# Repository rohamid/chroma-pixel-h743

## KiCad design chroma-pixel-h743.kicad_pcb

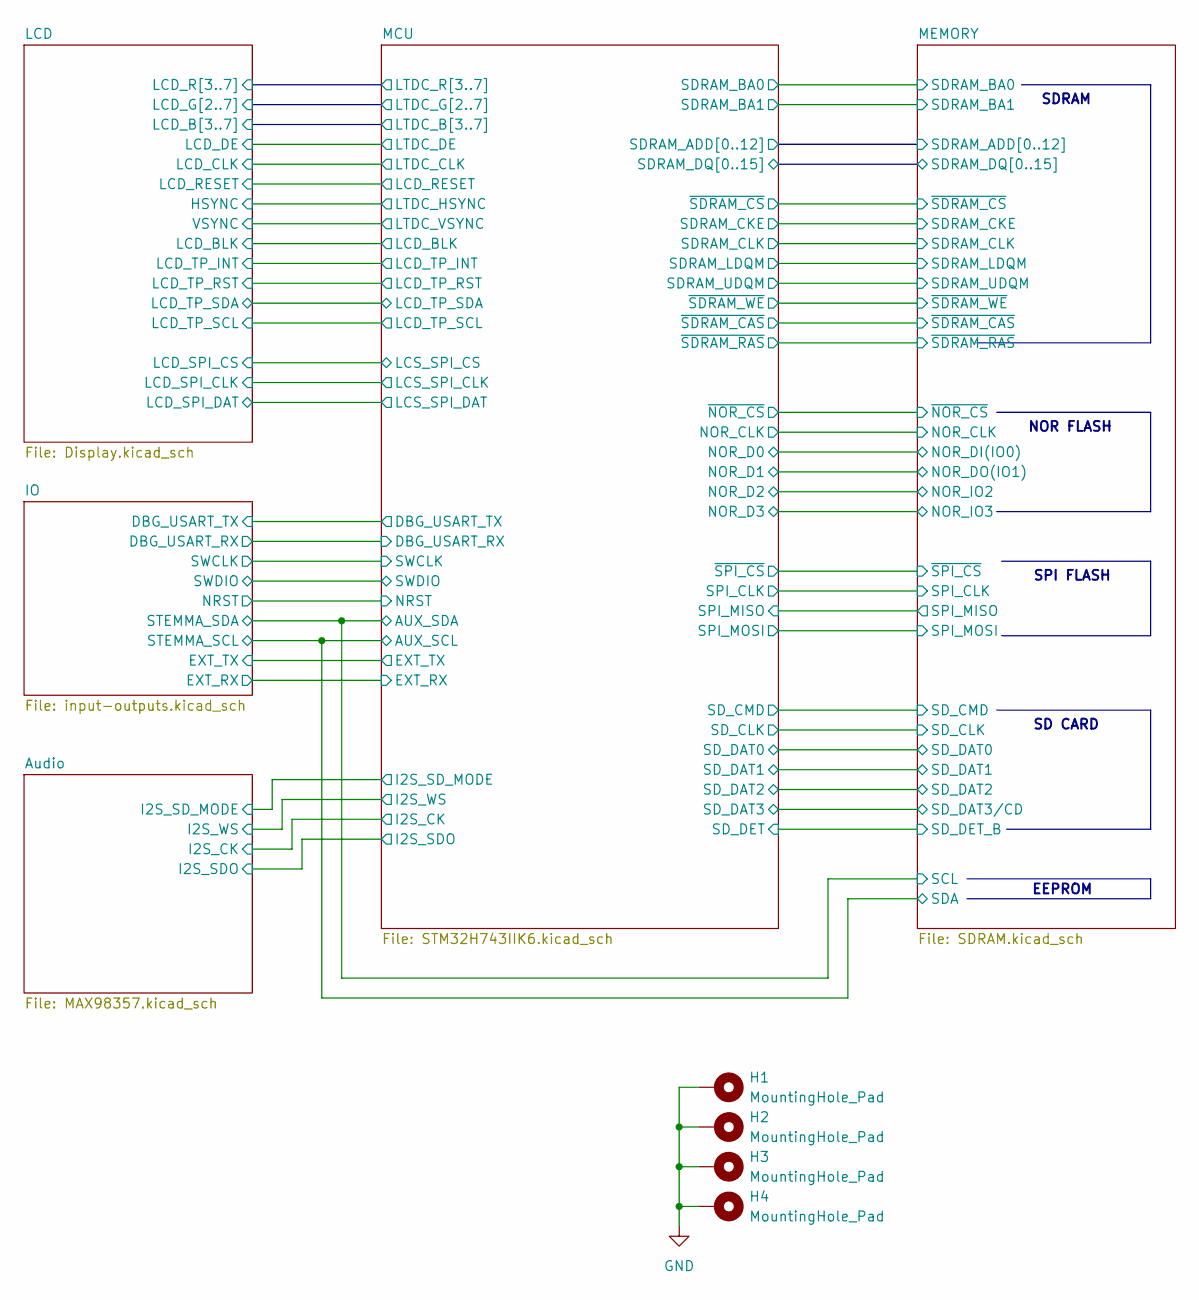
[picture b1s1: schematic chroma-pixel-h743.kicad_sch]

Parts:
H1, H2, H3, H4: MountingHole_Pad; MountingHole_3.2mm_M3_Pad_Via

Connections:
GND: H1.1, H2.1, H3.1, H4.1; also elsewhere on the board

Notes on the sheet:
SD CARD
NOR FLASH
SPI FLASH
SDRAM
EEPROM

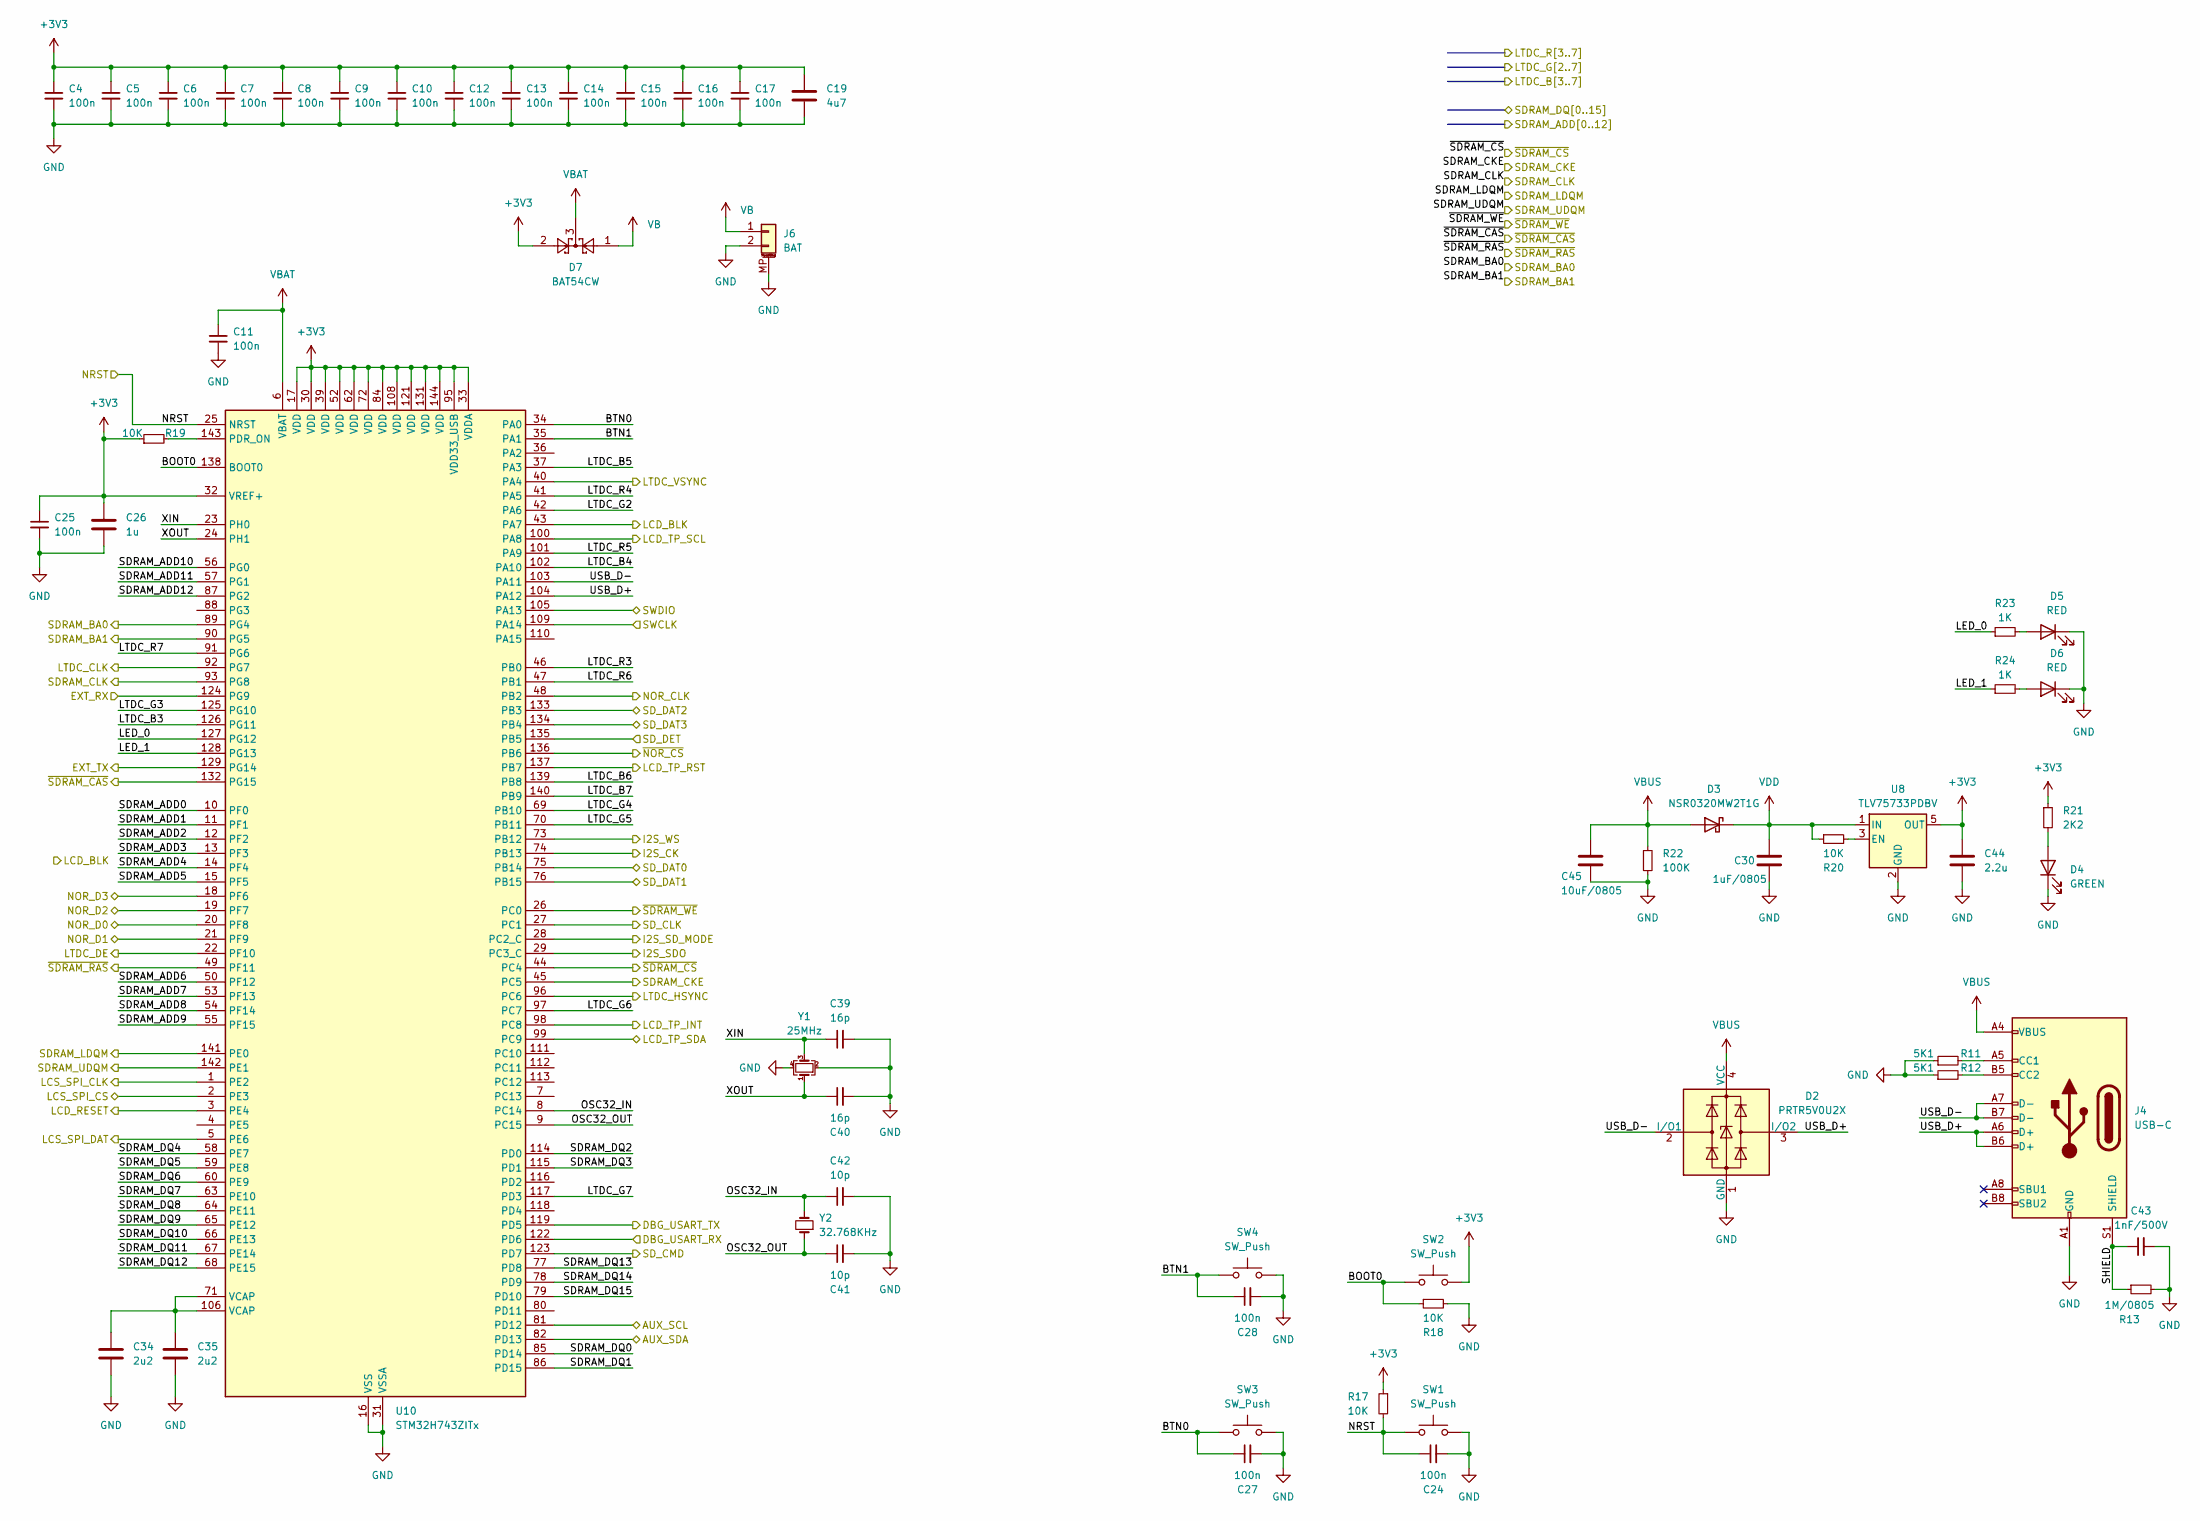
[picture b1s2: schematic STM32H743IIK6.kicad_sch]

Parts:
C4, C5, C6, C7, C8, C9, C10, C11, C12, C13, C14, C15, C16, C17, C24, C25, C27, C28: 100n; C_0402_1005Metric; JLCPCB Part # C307331
C19: 4u7; C_0603_1608Metric; JLCPCB Part # C19666
C26: 1u; C_0603_1608Metric; JLCPCB Part # C15849
C30: 1uF/0805; C_0805_2012Metric; JLCPCB Part # C28323
C34, C35: 2u2; C_0603_1608Metric; JLCPCB Part # C23630
C39, C40: 16p; C_0402_1005Metric; JLCPCB Part # C77590
C41, C42: 10p; C_0402_1005Metric; JLCPCB Part # C32949
C43: 1nF/500V; C_1206_3216Metric; JLCPCB Part # C35216
C44: 2.2u; C_0805_2012Metric; JLCPCB Part # C377773
C45: 10uF/0805; C_0805_2012Metric; JLCPCB Part # C440198
D2: PRTR5V0U2X; SOT-143; JLCPCB Part # C12333
D3: NSR0320MW2T1G; D_SOD-323; JLCPCB Part # C48192
D4: GREEN; LED_0805_2012Metric; JLCPCB Part # C2297
D5, D6: RED; LED_0805_2012Metric; JLCPCB Part # C84256
D7: BAT54CW; SOT-23; JLCPCB Part # C37704
J4: USB-C; USB_C_Receptacle_G-Switch_GT-USB-7010ASV; JLCPCB Part # C963412
J6: BAT; Hirose_DF13C_CL535-0402-2-51_1x02-1MP_P1.25mm_Vertical; JLCPCB Part # C7419891
R11, R12: 5K1; R_0402_1005Metric; JLCPCB Part # C25905
R13: 1M/0805; R_0805_2012Metric; JLCPCB Part # C17514
R17, R18, R19, R20: 10K; R_0402_1005Metric; JLCPCB Part # C25744
R21: 2K2; R_0402_1005Metric; JLCPCB Part # C25879
R22: 100K; R_0402_1005Metric; JLCPCB Part # C60491
R23, R24: 1K; R_0402_1005Metric; JLCPCB Part # C11702
SW1, SW2, SW3, SW4: SW_Push; SW_SPST_PTS810; JLCPCB Part # C127488
U8: TLV75733PDBV; SOT-23-5; JLCPCB Part # C485517
U10: STM32H743ZITx; LQFP-144_20x20mm_P0.5mm; JLCPCB Part # C114408
Y1: 25MHz; Crystal_SMD_2520-4Pin_2.5x2.0mm; JLCPCB Part # C255954
Y2: 32.768KHz; Crystal_SMD_2012-2Pin_2.0x1.2mm; JLCPCB Part # C99009

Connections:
+3V3: C4.1, C5.1, C6.1, C7.1, C8.1, C9.1, C10.1, C12.1, C13.1, C14.1, C15.1, C16.1, C17.1, C19.1, C25.1, C26.1, C44.1, D7.2, R17.1, R19.1, R21.1, SW2.2, U8.5 (OUT), U10.17 (VDD), U10.30 (VDD), U10.32 (VREF+), U10.33 (VDDA), U10.39 (VDD), U10.52 (VDD), U10.62 (VDD), U10.72 (VDD), U10.84 (VDD), U10.95 (VDD33_USB), U10.108 (VDD), U10.121 (VDD), U10.131 (VDD), U10.144 (VDD); also elsewhere on the board
/Audio/I2S_CK: U10.74 (PB13); also elsewhere on the board
/Audio/I2S_SDO: U10.29 (PC3_C); also elsewhere on the board
/Audio/I2S_SD_MODE: U10.28 (PC2_C); also elsewhere on the board
/Audio/I2S_WS: U10.73 (PB12); also elsewhere on the board
/IO/DBG_USART_RX: U10.122 (PD6); also elsewhere on the board
/IO/DBG_USART_TX: U10.119 (PD5); also elsewhere on the board
/IO/EXT_RX: U10.124 (PG9); also elsewhere on the board
/IO/EXT_TX: U10.129 (PG14); also elsewhere on the board
/IO/NRST: C24.1, R17.2, SW1.1, U10.25 (NRST); also elsewhere on the board
/IO/STEMMA_SCL: U10.81 (PD12); also elsewhere on the board
/IO/STEMMA_SDA: U10.82 (PD13); also elsewhere on the board
/IO/SWCLK: U10.109 (PA14); also elsewhere on the board
/IO/SWDIO: U10.105 (PA13); also elsewhere on the board
/LCD/HSYNC: U10.96 (PC6); also elsewhere on the board
/LCD/LCD_B3: U10.126 (PG11); also elsewhere on the board
/LCD/LCD_B4: U10.102 (PA10); also elsewhere on the board
/LCD/LCD_B5: U10.37 (PA3); also elsewhere on the board
/LCD/LCD_B6: U10.139 (PB8); also elsewhere on the board
/LCD/LCD_B7: U10.140 (PB9); also elsewhere on the board
/LCD/LCD_BLK: U10.43 (PA7); also elsewhere on the board
/LCD/LCD_CLK: U10.92 (PG7); also elsewhere on the board
/LCD/LCD_DE: U10.22 (PF10); also elsewhere on the board
/LCD/LCD_G2: U10.42 (PA6); also elsewhere on the board
/LCD/LCD_G3: U10.125 (PG10); also elsewhere on the board
/LCD/LCD_G4: U10.69 (PB10); also elsewhere on the board
/LCD/LCD_G5: U10.70 (PB11); also elsewhere on the board
/LCD/LCD_G6: U10.97 (PC7); also elsewhere on the board
/LCD/LCD_G7: U10.117 (PD3); also elsewhere on the board
/LCD/LCD_R3: U10.46 (PB0); also elsewhere on the board
/LCD/LCD_R4: U10.41 (PA5); also elsewhere on the board
/LCD/LCD_R5: U10.101 (PA9); also elsewhere on the board
/LCD/LCD_R6: U10.47 (PB1); also elsewhere on the board
/LCD/LCD_R7: U10.91 (PG6); also elsewhere on the board
/LCD/LCD_RESET: U10.3 (PE4); also elsewhere on the board
/LCD/LCD_SPI_CLK: U10.1 (PE2); also elsewhere on the board
/LCD/LCD_SPI_CS: U10.2 (PE3); also elsewhere on the board
/LCD/LCD_SPI_DAT: U10.5 (PE6); also elsewhere on the board
/LCD/LCD_TP_INT: U10.98 (PC8); also elsewhere on the board
/LCD/LCD_TP_RST: U10.137 (PB7); also elsewhere on the board
/LCD/LCD_TP_SCL: U10.100 (PA8); also elsewhere on the board
/LCD/LCD_TP_SDA: U10.99 (PC9); also elsewhere on the board
/LCD/VSYNC: U10.40 (PA4); also elsewhere on the board
/MCU/BOOT0: R18.1, SW2.1, U10.138 (BOOT0)
/MCU/BTN0: C27.1, SW3.1, U10.34 (PA0)
/MCU/BTN1: C28.1, SW4.1, U10.35 (PA1)
/MCU/LED_0: R23.1, U10.127 (PG12)
/MCU/LED_1: R24.1, U10.128 (PG13)
/MCU/OSC32_IN: C42.1, U10.8 (PC14), Y2.2
/MCU/OSC32_OUT: C41.1, U10.9 (PC15), Y2.1
/MCU/SDRAM_ADD0: U10.10 (PF0); also elsewhere on the board
/MCU/SDRAM_ADD1: U10.11 (PF1); also elsewhere on the board
/MCU/SDRAM_ADD2: U10.12 (PF2); also elsewhere on the board
/MCU/SDRAM_ADD3: U10.13 (PF3); also elsewhere on the board
/MCU/SDRAM_ADD4: U10.14 (PF4); also elsewhere on the board
/MCU/SDRAM_ADD5: U10.15 (PF5); also elsewhere on the board
/MCU/SDRAM_ADD6: U10.50 (PF12); also elsewhere on the board
/MCU/SDRAM_ADD7: U10.53 (PF13); also elsewhere on the board
/MCU/SDRAM_ADD8: U10.54 (PF14); also elsewhere on the board
/MCU/SDRAM_ADD9: U10.55 (PF15); also elsewhere on the board
/MCU/SDRAM_ADD10: U10.56 (PG0); also elsewhere on the board
/MCU/SDRAM_ADD11: U10.57 (PG1); also elsewhere on the board
/MCU/SDRAM_ADD12: U10.87 (PG2); also elsewhere on the board
/MCU/SDRAM_BA0: U10.89 (PG4); also elsewhere on the board
/MCU/SDRAM_BA1: U10.90 (PG5); also elsewhere on the board
/MCU/SDRAM_CKE: U10.45 (PC5); also elsewhere on the board
/MCU/SDRAM_CLK: U10.93 (PG8); also elsewhere on the board
/MCU/SDRAM_DQ0: U10.85 (PD14); also elsewhere on the board
/MCU/SDRAM_DQ1: U10.86 (PD15); also elsewhere on the board
/MCU/SDRAM_DQ2: U10.114 (PD0); also elsewhere on the board
/MCU/SDRAM_DQ3: U10.115 (PD1); also elsewhere on the board
/MCU/SDRAM_DQ4: U10.58 (PE7); also elsewhere on the board
/MCU/SDRAM_DQ5: U10.59 (PE8); also elsewhere on the board
/MCU/SDRAM_DQ6: U10.60 (PE9); also elsewhere on the board
/MCU/SDRAM_DQ7: U10.63 (PE10); also elsewhere on the board
/MCU/SDRAM_DQ8: U10.64 (PE11); also elsewhere on the board
/MCU/SDRAM_DQ9: U10.65 (PE12); also elsewhere on the board
/MCU/SDRAM_DQ10: U10.66 (PE13); also elsewhere on the board
/MCU/SDRAM_DQ11: U10.67 (PE14); also elsewhere on the board
/MCU/SDRAM_DQ12: U10.68 (PE15); also elsewhere on the board
/MCU/SDRAM_DQ13: U10.77 (PD8); also elsewhere on the board
/MCU/SDRAM_DQ14: U10.78 (PD9); also elsewhere on the board
/MCU/SDRAM_DQ15: U10.79 (PD10); also elsewhere on the board
/MCU/SDRAM_LDQM: U10.141 (PE0); also elsewhere on the board
/MCU/SDRAM_UDQM: U10.142 (PE1); also elsewhere on the board
/MCU/SHIELD: C43.1, J4.S1 (SHIELD), R13.1
/MCU/USB_D+: D2.3 (I/O2), J4.A6 (D+), J4.B6 (D+), U10.104 (PA12)
/MCU/USB_D-: D2.2 (I/O1), J4.A7 (D-), J4.B7 (D-), U10.103 (PA11)
/MCU/XIN: C39.1, U10.23 (PH0), Y1.3
/MCU/XOUT: C40.1, U10.24 (PH1), Y1.1
/MCU/~SDRAM_CAS: U10.132 (PG15); also elsewhere on the board
/MCU/~SDRAM_CS: U10.44 (PC4); also elsewhere on the board
/MCU/~SDRAM_RAS: U10.49 (PF11); also elsewhere on the board
/MCU/~SDRAM_WE: U10.26 (PC0); also elsewhere on the board
/MEMORY/NOR_CLK: U10.48 (PB2); also elsewhere on the board
/MEMORY/NOR_DI(IO0): U10.20 (PF8); also elsewhere on the board
/MEMORY/NOR_DO(IO1): U10.21 (PF9); also elsewhere on the board
/MEMORY/NOR_IO2: U10.19 (PF7); also elsewhere on the board
/MEMORY/NOR_IO3: U10.18 (PF6); also elsewhere on the board
/MEMORY/SD_CLK: U10.27 (PC1); also elsewhere on the board
/MEMORY/SD_CMD: U10.123 (PD7); also elsewhere on the board
/MEMORY/SD_DAT0: U10.75 (PB14); also elsewhere on the board
/MEMORY/SD_DAT1: U10.76 (PB15); also elsewhere on the board
/MEMORY/SD_DAT2: U10.133 (PB3); also elsewhere on the board
/MEMORY/SD_DAT3/CD: U10.134 (PB4); also elsewhere on the board
/MEMORY/SD_DET: U10.135 (PB5); also elsewhere on the board
/MEMORY/~NOR_CS: U10.136 (PB6); also elsewhere on the board
GND: C4.2, C5.2, C6.2, C7.2, C8.2, C9.2, C10.2, C11.2, C12.2, C13.2, C14.2, C15.2, C16.2, C17.2, C19.2, C24.2, C25.2, C26.2, C27.2, C28.2, C30.2, C34.2, C35.2, C39.2, C40.2, C41.2, C42.2, C43.2, C44.2, C45.2, D2.1 (GND), D4.1 (K), D5.1 (K), D6.1 (K), J4.A1 (GND), J4.A12 (GND), J4.B1 (GND), J4.B12 (GND), J6.2, J6.MP (MountPin), R11.1, R12.1, R13.2, R18.2, R22.2, SW1.2, SW3.2, SW4.2, U8.2 (GND), U10.16 (VSS), U10.31 (VSSA), U10.38 (VSS), U10.51 (VSS), U10.61 (VSS), U10.83 (VSS), U10.94 (VSS), U10.107 (VSS), U10.120 (VSS), U10.130 (VSS), Y1.2, Y1.4; also elsewhere on the board
unnamed: C34.1, C35.1, U10.71 (VCAP), U10.106 (VCAP)
unnamed: D4.2 (A), R21.2
unnamed: D5.2 (A), R23.2
unnamed: D6.2 (A), R24.2
unnamed: J4.A5 (CC1), R11.2
unnamed: J4.B5 (CC2), R12.2
unnamed: R20.2, U8.3 (EN)
unnamed: R19.2, U10.143 (PDR_ON)
VB: D7.1, J6.1
VBAT: C11.1, D7.3, U10.6 (VBAT)
VBUS: C45.1, D2.4 (VCC), D3.2 (A), J4.A4 (VBUS), J4.A9 (VBUS), J4.B4 (VBUS), J4.B9 (VBUS), R22.1; also elsewhere on the board
VDD: C30.1, D3.1 (K), R20.1, U8.1 (IN); also elsewhere on the board

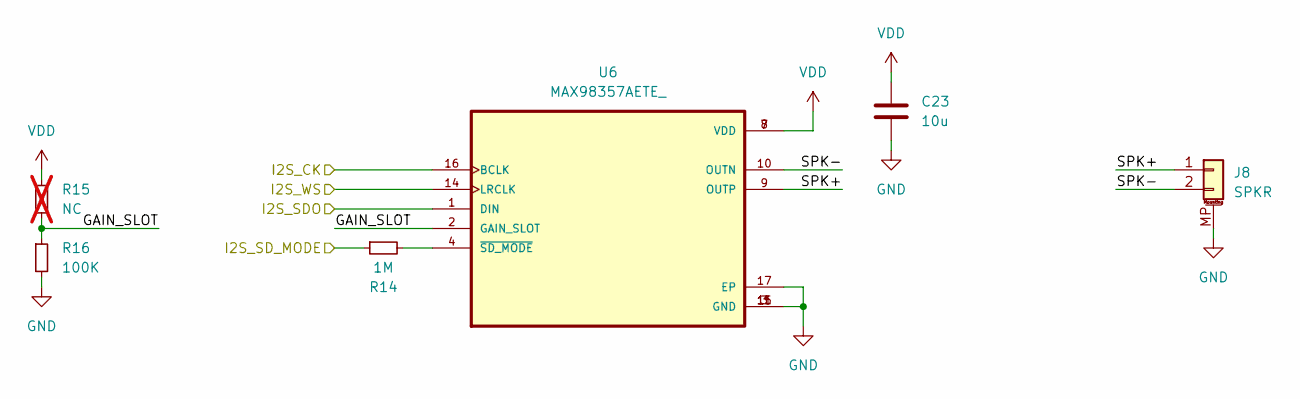
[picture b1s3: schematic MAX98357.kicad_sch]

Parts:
C23: 10u; C_0603_1608Metric; JLCPCB Part # C96446
J8: SPKR; Hirose_DF13C_CL535-0402-2-51_1x02-1MP_P1.25mm_Vertical; JLCPCB Part # C7419891
R14: 1M; R_0402_1005Metric; JLCPCB Part # C26083
R15: NC; R_0402_1005Metric; not fitted
R16: 100K; R_0402_1005Metric; JLCPCB Part # C60491
U6: MAX98357AETE_; QFN50P300X300X80-17N; JLCPCB Part # C910544

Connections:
/Audio/GAIN_SLOT: R15.2, R16.1, U6.2 (GAIN_SLOT)
/Audio/I2S_CK: U6.16 (BCLK); also elsewhere on the board
/Audio/I2S_SDO: U6.1 (DIN); also elsewhere on the board
/Audio/I2S_SD_MODE: R14.1; also elsewhere on the board
/Audio/I2S_WS: U6.14 (LRCLK); also elsewhere on the board
/Audio/SPK+: J8.1, U6.9 (OUTP)
/Audio/SPK-: J8.2, U6.10 (OUTN)
GND: C23.2, J8.MP (MountPin), R16.2, U6.3 (GND), U6.11 (GND), U6.15 (GND), U6.17 (EP); also elsewhere on the board
unnamed: R14.2, U6.4 (~SD_MODE)
VDD: C23.1, R15.1, U6.7 (VDD), U6.8 (VDD); also elsewhere on the board

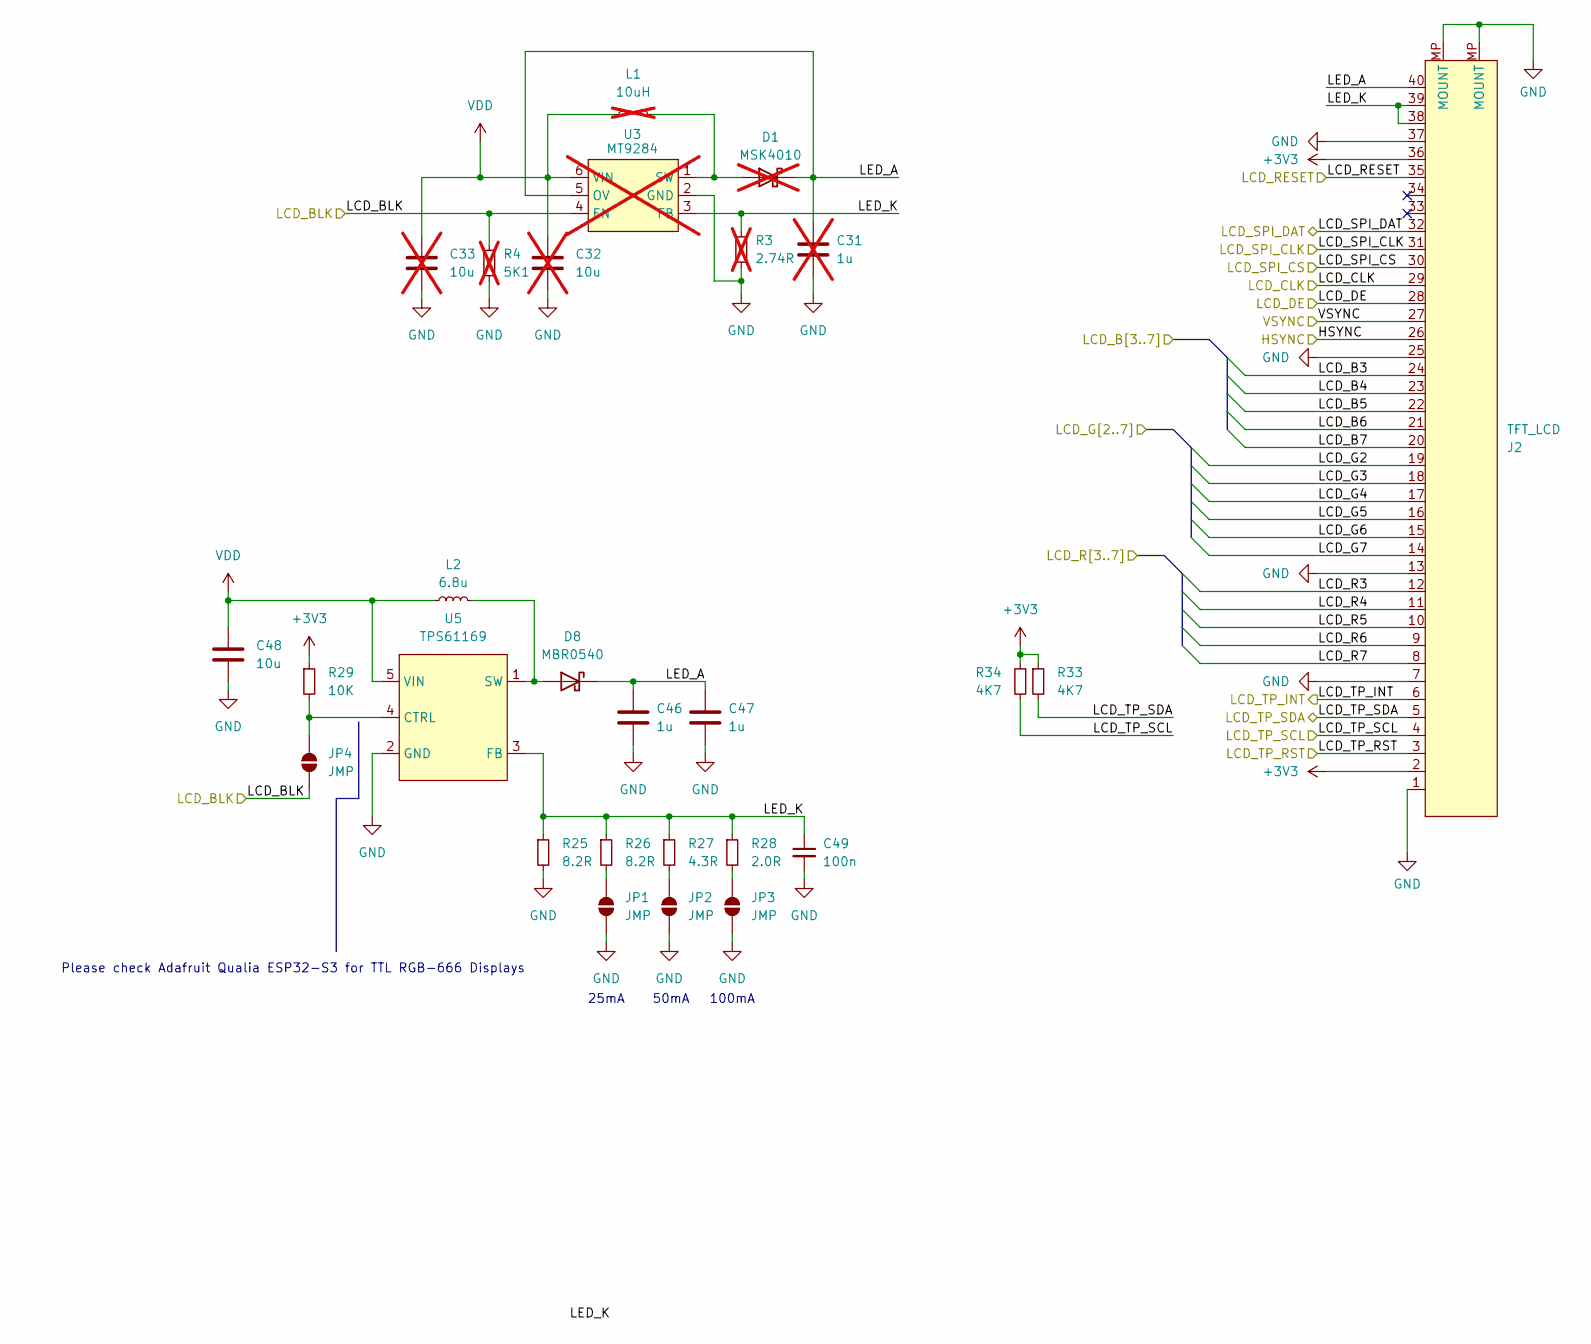
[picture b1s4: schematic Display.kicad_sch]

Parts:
C31: 1u; C_0603_1608Metric; JLCPCB Part # C15849; not fitted
C32, C33: 10u; C_0603_1608Metric; JLCPCB Part # C96446; not fitted
C46, C47: 1u; C_0603_1608Metric; JLCPCB Part # C15849
C48: 10u; C_0603_1608Metric; JLCPCB Part # C96446
C49: 100n; C_0402_1005Metric; JLCPCB Part # C307331
D1: MSK4010; D_SOD-523; JLCPCB Part # C345958; not fitted
D8: MBR0540; D_SOD-123; JLCPCB Part # C21353
J2: TFT_LCD; Omron-XF2M-4015-1A-R100-0-0-0; JLCPCB Part # C225713
JP1, JP2, JP3, JP4: JMP; SolderJumper-2_P1.3mm_Open_RoundedPad1.0x1.5mm
L1: 10uH; L_1210_3225Metric; JLCPCB Part # C189932; not fitted
L2: 6.8u; L_1210_3225Metric; JLCPCB Part # C844992
R3: 2.74R; R_0402_1005Metric; JLCPCB Part # C166483; not fitted
R4: 5K1; R_0402_1005Metric; JLCPCB Part # C25905; not fitted
R25, R26: 8.2R; R_0402_1005Metric; JLCPCB Part # C514788
R27: 4.3R; R_0402_1005Metric; JLCPCB Part # C166641
R28: 2.0R; R_0402_1005Metric; JLCPCB Part # C203084
R29: 10K; R_0402_1005Metric; JLCPCB Part # C25744
R33, R34: 4K7; R_0402_1005Metric; JLCPCB Part # C203084
U3: MT9284; SOT-23-6; JLCPCB Part # C181780; not fitted
U5: TPS61169; SOT-353_SC-70-5; JLCPCB Part # C71045

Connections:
+3V3: J2.2, J2.36, R29.1, R33.1, R34.1; also elsewhere on the board
/LCD/HSYNC: J2.26; also elsewhere on the board
/LCD/LCD_B3: J2.24; also elsewhere on the board
/LCD/LCD_B4: J2.23; also elsewhere on the board
/LCD/LCD_B5: J2.22; also elsewhere on the board
/LCD/LCD_B6: J2.21; also elsewhere on the board
/LCD/LCD_B7: J2.20; also elsewhere on the board
/LCD/LCD_BLK: JP4.1 (A), R4.1, U3.4 (EN); also elsewhere on the board
/LCD/LCD_CLK: J2.29; also elsewhere on the board
/LCD/LCD_DE: J2.28; also elsewhere on the board
/LCD/LCD_G2: J2.19; also elsewhere on the board
/LCD/LCD_G3: J2.18; also elsewhere on the board
/LCD/LCD_G4: J2.17; also elsewhere on the board
/LCD/LCD_G5: J2.16; also elsewhere on the board
/LCD/LCD_G6: J2.15; also elsewhere on the board
/LCD/LCD_G7: J2.14; also elsewhere on the board
/LCD/LCD_R3: J2.12; also elsewhere on the board
/LCD/LCD_R4: J2.11; also elsewhere on the board
/LCD/LCD_R5: J2.10; also elsewhere on the board
/LCD/LCD_R6: J2.9; also elsewhere on the board
/LCD/LCD_R7: J2.8; also elsewhere on the board
/LCD/LCD_RESET: J2.35; also elsewhere on the board
/LCD/LCD_SPI_CLK: J2.31; also elsewhere on the board
/LCD/LCD_SPI_CS: J2.30; also elsewhere on the board
/LCD/LCD_SPI_DAT: J2.32; also elsewhere on the board
/LCD/LCD_TP_INT: J2.6; also elsewhere on the board
/LCD/LCD_TP_RST: J2.3; also elsewhere on the board
/LCD/LCD_TP_SCL: J2.4, R34.2; also elsewhere on the board
/LCD/LCD_TP_SDA: J2.5, R33.2; also elsewhere on the board
/LCD/LED_A: C31.1, C46.1, C47.1, D1.1 (K), D8.1 (K), J2.40, U3.5 (OV)
/LCD/LED_K: C49.1, J2.38, J2.39, R3.1, R25.1, R26.1, R27.1, R28.1, U3.3 (FB), U5.3 (FB)
/LCD/VSYNC: J2.27; also elsewhere on the board
GND: C31.2, C32.2, C33.2, C46.2, C47.2, C48.2, C49.2, J2.1, J2.7, J2.13, J2.25, J2.37, J2.MP (MOUNT), JP1.1 (A), JP2.1 (A), JP3.1 (A), R3.2, R4.2, R25.2, U3.2 (GND), U5.2 (GND); also elsewhere on the board
unnamed: D1.2 (A), L1.2, U3.1 (SW)
unnamed: D8.2 (A), L2.2, U5.1 (SW)
unnamed: JP1.2 (B), R26.2
unnamed: JP2.2 (B), R27.2
unnamed: JP3.2 (B), R28.2
unnamed: JP4.2 (B), R29.2, U5.4 (CTRL)
VDD: C32.1, C33.1, C48.1, L1.1, L2.1, U3.6 (VIN), U5.5 (VIN); also elsewhere on the board

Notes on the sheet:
100mA
50mA
25mA
Please check Adafruit Qualia ESP32-S3 for TTL RGB-666 Displays

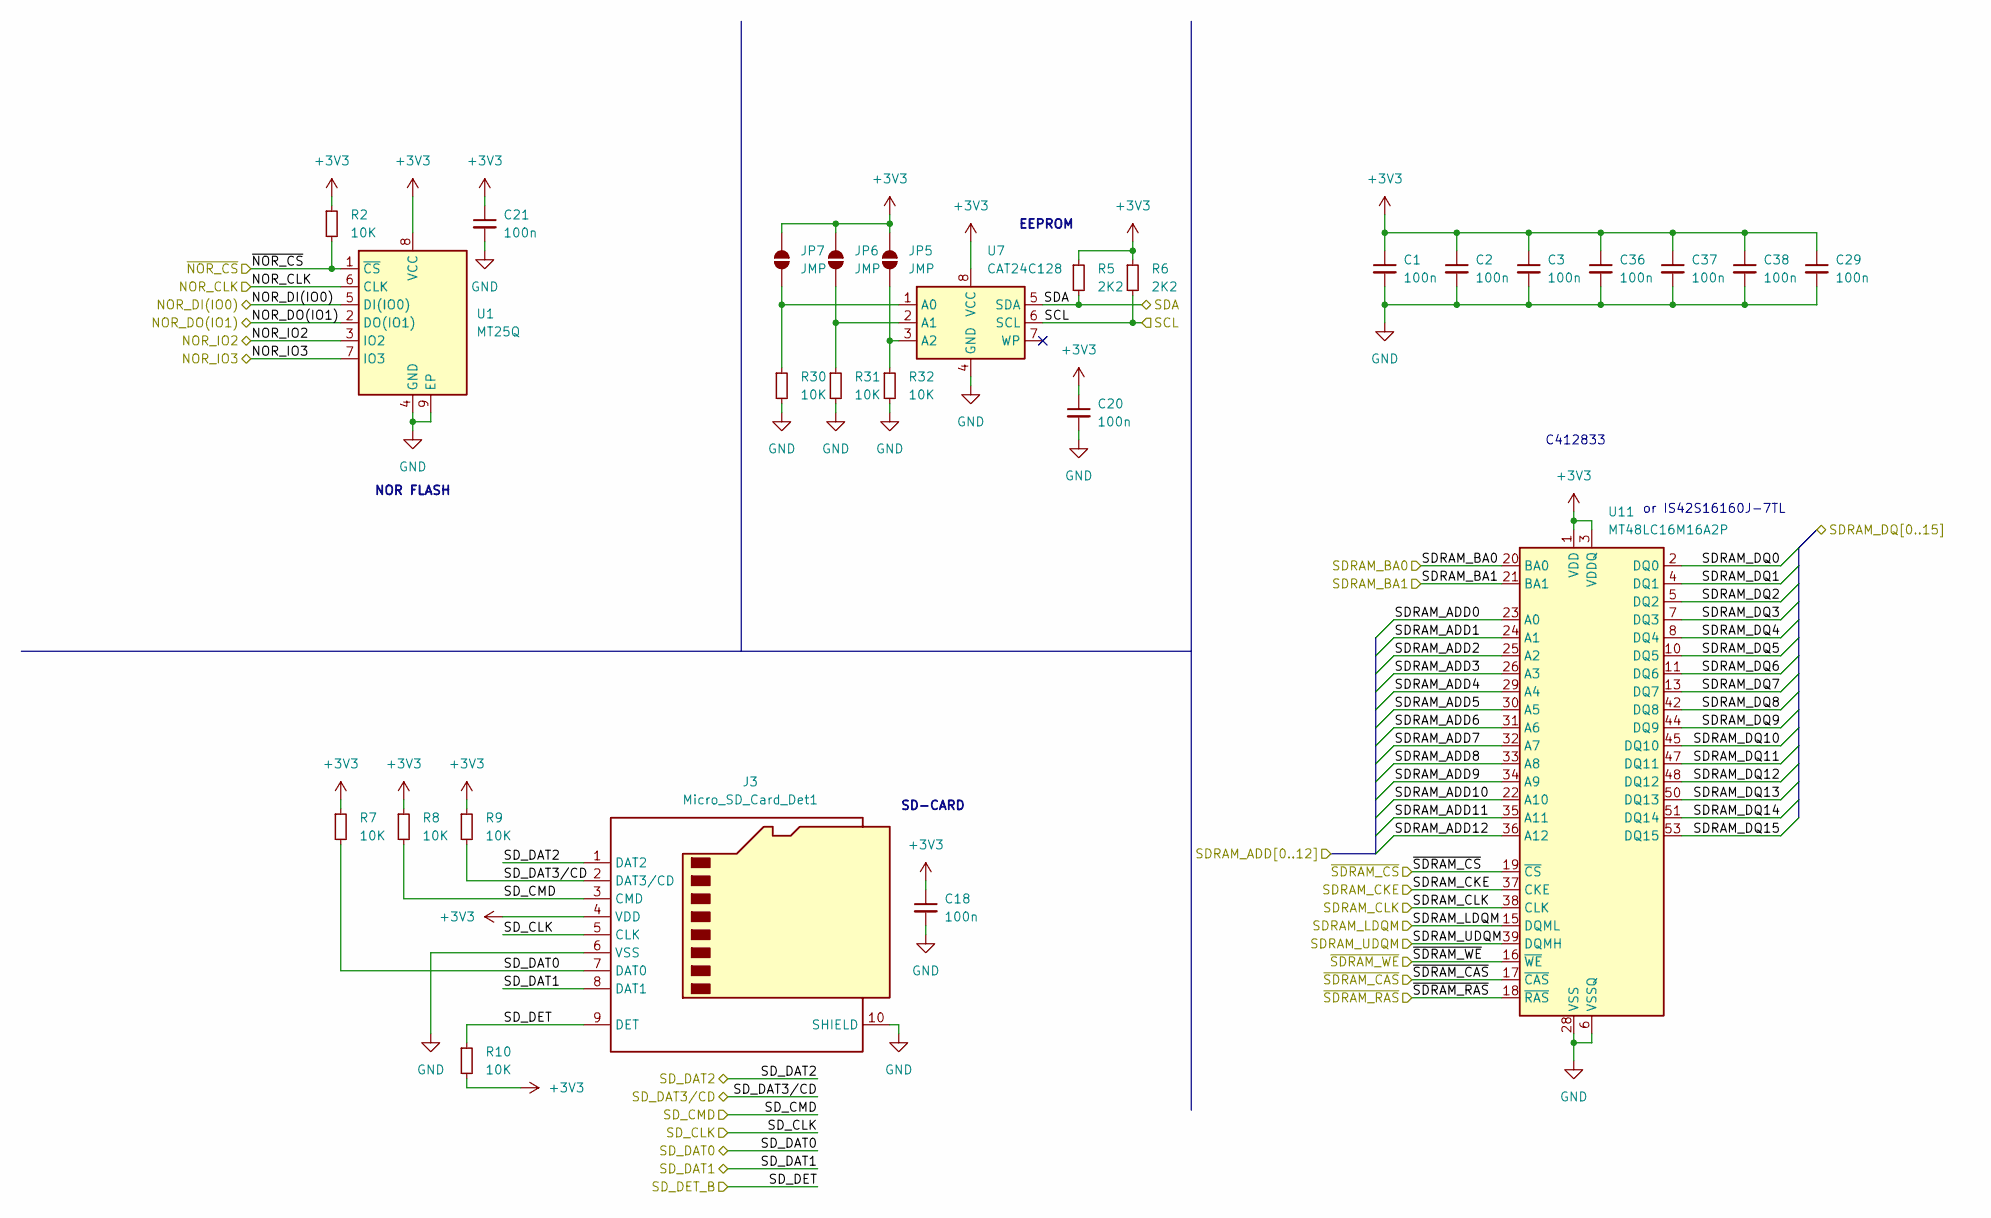
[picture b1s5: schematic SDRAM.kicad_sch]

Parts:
C1, C2, C3, C18, C20, C21, C29, C36, C37, C38: 100n; C_0402_1005Metric; JLCPCB Part # C307331
J3: Micro_SD_Card_Det1; SD-TF-115; JLCPCB Part # C266621
JP5, JP6, JP7: JMP; SolderJumper-2_P1.3mm_Open_RoundedPad1.0x1.5mm
R2, R7, R8, R9, R10, R30, R31, R32: 10K; R_0402_1005Metric; JLCPCB Part # C25744
R5, R6: 2K2; R_0402_1005Metric; JLCPCB Part # C25879
U1: MT25Q; WSON-8-1EP_8x6mm_P1.27mm_EP3.4x4.3mm; JLCPCB Part # C2061007
U7: CAT24C128; SOIC-8_3.9x4.9mm_P1.27mm; JLCPCB Part # C6482
U11: MT48LC16M16A2P; TSOP-II-54_22.2x10.16mm_P0.8mm; JLCPCB Part # C412833

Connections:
+3V3: C1.1, C2.1, C3.1, C18.1, C20.1, C21.1, C29.1, C36.1, C37.1, C38.1, J3.4 (VDD), JP5.2 (B), JP6.2 (B), JP7.2 (B), R2.1, R5.1, R6.1, R7.1, R8.1, R9.1, R10.2, U1.8 (VCC), U7.8 (VCC), U11.1 (VDD), U11.3 (VDDQ), U11.9 (VDDQ), U11.14 (VDD), U11.27 (VDD), U11.43 (VDDQ), U11.49 (VDDQ); also elsewhere on the board
/IO/STEMMA_SCL: R5.2, U7.5 (SDA); also elsewhere on the board
/IO/STEMMA_SDA: R6.2, U7.6 (SCL); also elsewhere on the board
/MCU/SDRAM_ADD0: U11.23 (A0); also elsewhere on the board
/MCU/SDRAM_ADD1: U11.24 (A1); also elsewhere on the board
/MCU/SDRAM_ADD2: U11.25 (A2); also elsewhere on the board
/MCU/SDRAM_ADD3: U11.26 (A3); also elsewhere on the board
/MCU/SDRAM_ADD4: U11.29 (A4); also elsewhere on the board
/MCU/SDRAM_ADD5: U11.30 (A5); also elsewhere on the board
/MCU/SDRAM_ADD6: U11.31 (A6); also elsewhere on the board
/MCU/SDRAM_ADD7: U11.32 (A7); also elsewhere on the board
/MCU/SDRAM_ADD8: U11.33 (A8); also elsewhere on the board
/MCU/SDRAM_ADD9: U11.34 (A9); also elsewhere on the board
/MCU/SDRAM_ADD10: U11.22 (A10); also elsewhere on the board
/MCU/SDRAM_ADD11: U11.35 (A11); also elsewhere on the board
/MCU/SDRAM_ADD12: U11.36 (A12); also elsewhere on the board
/MCU/SDRAM_BA0: U11.20 (BA0); also elsewhere on the board
/MCU/SDRAM_BA1: U11.21 (BA1); also elsewhere on the board
/MCU/SDRAM_CKE: U11.37 (CKE); also elsewhere on the board
/MCU/SDRAM_CLK: U11.38 (CLK); also elsewhere on the board
/MCU/SDRAM_DQ0: U11.2 (DQ0); also elsewhere on the board
/MCU/SDRAM_DQ1: U11.4 (DQ1); also elsewhere on the board
/MCU/SDRAM_DQ2: U11.5 (DQ2); also elsewhere on the board
/MCU/SDRAM_DQ3: U11.7 (DQ3); also elsewhere on the board
/MCU/SDRAM_DQ4: U11.8 (DQ4); also elsewhere on the board
/MCU/SDRAM_DQ5: U11.10 (DQ5); also elsewhere on the board
/MCU/SDRAM_DQ6: U11.11 (DQ6); also elsewhere on the board
/MCU/SDRAM_DQ7: U11.13 (DQ7); also elsewhere on the board
/MCU/SDRAM_DQ8: U11.42 (DQ8); also elsewhere on the board
/MCU/SDRAM_DQ9: U11.44 (DQ9); also elsewhere on the board
/MCU/SDRAM_DQ10: U11.45 (DQ10); also elsewhere on the board
/MCU/SDRAM_DQ11: U11.47 (DQ11); also elsewhere on the board
/MCU/SDRAM_DQ12: U11.48 (DQ12); also elsewhere on the board
/MCU/SDRAM_DQ13: U11.50 (DQ13); also elsewhere on the board
/MCU/SDRAM_DQ14: U11.51 (DQ14); also elsewhere on the board
/MCU/SDRAM_DQ15: U11.53 (DQ15); also elsewhere on the board
/MCU/SDRAM_LDQM: U11.15 (DQML); also elsewhere on the board
/MCU/SDRAM_UDQM: U11.39 (DQMH); also elsewhere on the board
/MCU/~SDRAM_CAS: U11.17 (~CAS); also elsewhere on the board
/MCU/~SDRAM_CS: U11.19 (~CS); also elsewhere on the board
/MCU/~SDRAM_RAS: U11.18 (~RAS); also elsewhere on the board
/MCU/~SDRAM_WE: U11.16 (~WE); also elsewhere on the board
/MEMORY/NOR_CLK: U1.6 (CLK); also elsewhere on the board
/MEMORY/NOR_DI(IO0): U1.5 (DI(IO0)); also elsewhere on the board
/MEMORY/NOR_DO(IO1): U1.2 (DO(IO1)); also elsewhere on the board
/MEMORY/NOR_IO2: U1.3 (IO2); also elsewhere on the board
/MEMORY/NOR_IO3: U1.7 (IO3); also elsewhere on the board
/MEMORY/SD_CLK: J3.5 (CLK); also elsewhere on the board
/MEMORY/SD_CMD: J3.3 (CMD), R8.2; also elsewhere on the board
/MEMORY/SD_DAT0: J3.7 (DAT0), R7.2; also elsewhere on the board
/MEMORY/SD_DAT1: J3.8 (DAT1); also elsewhere on the board
/MEMORY/SD_DAT2: J3.1 (DAT2); also elsewhere on the board
/MEMORY/SD_DAT3/CD: J3.2 (DAT3/CD), R9.2; also elsewhere on the board
/MEMORY/SD_DET: J3.9 (DET), R10.1; also elsewhere on the board
/MEMORY/~NOR_CS: R2.2, U1.1 (~CS); also elsewhere on the board
GND: C1.2, C2.2, C3.2, C18.2, C20.2, C21.2, C29.2, C36.2, C37.2, C38.2, J3.6 (VSS), J3.10 (SHIELD), R30.2, R31.2, R32.2, U1.4 (GND), U1.9 (EP), U7.4 (GND), U11.6 (VSSQ), U11.12 (VSSQ), U11.28 (VSS), U11.41 (VSS), U11.46 (VSSQ), U11.52 (VSSQ), U11.54 (VSS); also elsewhere on the board
unnamed: JP5.1 (A), R32.1, U7.3 (A2)
unnamed: JP6.1 (A), R31.1, U7.2 (A1)
unnamed: JP7.1 (A), R30.1, U7.1 (A0)

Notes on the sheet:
C412833
NOR FLASH
SD-CARD
EEPROM
or IS42S16160J-7TL
